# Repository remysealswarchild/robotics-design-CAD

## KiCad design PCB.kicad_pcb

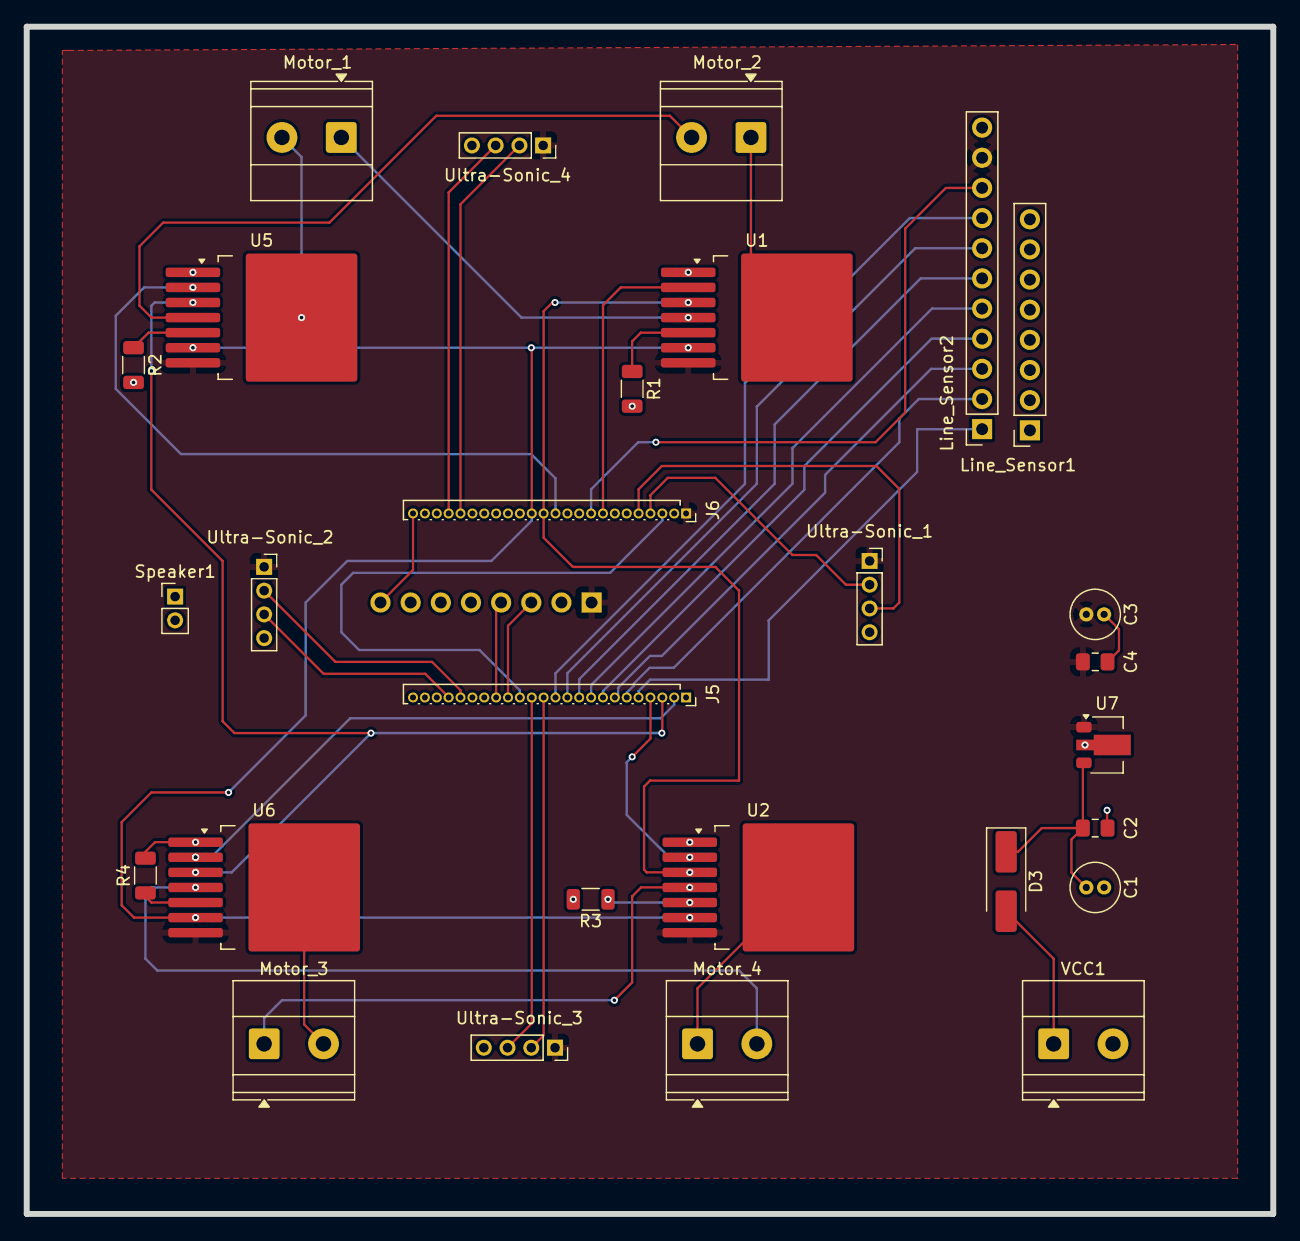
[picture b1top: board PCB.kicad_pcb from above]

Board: 2 copper layers, 105.0 x 100.0 mm, 29 parts (1 on the bottom side), 44 nets.

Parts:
C1, C3: C_US; C_Radial_D4.0mm_H5.0mm_P1.50mm
C2: 0.3u; C_0805_2012Metric_Pad1.18x1.45mm_HandSolder
C4: 0.1u; C_0805_2012Metric_Pad1.18x1.45mm_HandSolder
D3: D; D_SMA_Handsoldering
J5, J6: Conn_01x24_Socket; PinSocket_1x24_P1.00mm_Vertical
Line_Sensor1: Conn_01x08_Socket; PinSocket_1x08_P2.54mm_Vertical
Line_Sensor2: Conn_01x11_Socket; PinSocket_1x11_P2.54mm_Vertical
MEMS1: Conn_01x08_Socket; PinSocket_1x08_P2.54mm_Vertical
Motor_1, Motor_2, Motor_3, Motor_4: Screw_Terminal_01x02; TerminalBlock_Phoenix_MKDS-1,5-2_1x02_P5.00mm_Horizontal
R1, R2, R3, R4: 1K; R_1206_3216Metric
Speaker1: Conn_01x02_Socket; PinHeader_1x02_P2.00mm_Vertical
U1, U2, U5, U6: BTS7960B; Infineon_PG-TO-220-7Lead_TabPin8
U7: L78L05_SOT89; SOT-89-3
Ultra-Sonic_1, Ultra-Sonic_2, Ultra-Sonic_3, Ultra-Sonic_4: Conn_01x04_Socket; PinSocket_1x04_P2.00mm_Vertical
VCC1: Screw_Terminal_01x02; TerminalBlock_Phoenix_MKDS-1,5-2_1x02_P5.00mm_Horizontal

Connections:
3.3V: J5.15, J6.3
A/D_1: J5.5, Line_Sensor2.1
A/D_2: J5.6, Line_Sensor2.2
A/D_3: J5.7, Line_Sensor2.3
A/D_4: J5.8, Line_Sensor2.4
A/D_5: J5.9, Line_Sensor2.5
A/D_6: J5.10, Line_Sensor2.6
A/D_7: J5.11, Line_Sensor2.7
A/D_8: J5.12, Line_Sensor2.8
Echo_1: J6.5, Ultra-Sonic_1.3
Echo_2: J5.21, Ultra-Sonic_2.3
Echo_3: J5.14, Ultra-Sonic_3.3
Echo_4: J6.21, Ultra-Sonic_4.3
GND: C1.2, C2.2, C3.2, C4.2, J5.1, J6.2, J6.15, Line_Sensor1.1, Line_Sensor1.2, Line_Sensor1.3, Line_Sensor1.4, Line_Sensor1.5, Line_Sensor1.6, Line_Sensor2.11, MEMS1.2, R1.2, R2.2, R3.2, R4.2, U1.1 (GND), U2.1 (GND), U5.1 (GND), U6.1 (GND), U7.2 (GND), Ultra-Sonic_1.4, Ultra-Sonic_2.4, Ultra-Sonic_3.4, Ultra-Sonic_4.4, VCC1.2
INH A: J6.13, U1.3 (INH), U2.3 (INH)
INH B: J5.3, U5.3 (INH), U6.3 (INH)
IS: J6.14, U1.6 (IS), U2.6 (IS), U5.6 (IS), U6.6 (IS)
LED_ON: J6.9, Line_Sensor2.9
Motor 1-Out A: Motor_1.1, U1.4 (OUT)
Motor 1-Out B: Motor_1.2, U5.8 (OUT)
Motor 2-Out A: Motor_2.1, U1.8 (OUT)
Motor 2-Out B: Motor_2.2, U5.4 (OUT)
Motor 3-Out A: Motor_3.1, U2.4 (OUT)
Motor 3-Out B: Motor_3.2, U6.8 (OUT)
Motor 4-Out A: Motor_4.1, U2.8 (OUT)
Motor 4-Out B: Motor_4.2, U6.4 (OUT)
unnamed: D3.2 (A), VCC1.1
unnamed: C1.1, C2.1, D3.1 (K), U7.3 (IN)
unnamed: R1.1, U1.5 (SR)
unnamed: R3.1, U2.5 (SR)
unnamed: R2.1, U5.5 (SR)
unnamed: R4.1, U6.5 (SR)
PWM 1-Motor 1_2: J6.8, U1.2 (IN)
PWM 1-Motor 3_4: J5.4, U2.2 (IN)
PWM 2-Motor 1_2: J6.12, U5.2 (IN)
PWM 2-Motor 3_4: J5.2, U6.2 (IN)
PWM_INT: J6.24, MEMS1.8
SCL: J5.16, MEMS1.3
SDA: J5.17, MEMS1.4
Trig_1: J6.4, Ultra-Sonic_1.2
Trig_2: J5.20, Ultra-Sonic_2.2
Trig_3: J5.13, Ultra-Sonic_3.2
Trig_4: J6.20, Ultra-Sonic_4.2
Vcc_5V: C3.1, C4.1, J6.1, Line_Sensor2.10, MEMS1.1, U1.7 (VS), U2.7 (VS), U5.7 (VS), U6.7 (VS), U7.1 (OUT), Ultra-Sonic_1.1, Ultra-Sonic_2.1, Ultra-Sonic_3.1, Ultra-Sonic_4.1

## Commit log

2025-06-22 Initial commit with new project files
